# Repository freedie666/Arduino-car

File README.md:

# Arduino Car
  
Robotic car that follows line drawn on the ground using arduino.

Project was created at BUT-FIT

, class IMR.

## What robot does

> - Follows line at the ground
> - Can detect extra line that tells robot where to go at the crossroads
> - Extra lines can give robot additional orders
> - Detection of obstacle on the line
> - Robot can find best way around obstacle and avoid it
> - Is able to carry cargo and unload it on command
> - Sings a song when detects obstacle
> - Has multiple Blue and RED LEDs that show its intentions
> - Carries its own power source - batteries

## How its done

> - Brain of the operation is Arduino UNO
> - Car is powered by two 12V DC motors with gearbox
> - Motors are controlled by motor driver LV8406 using PWM
> - Lines are detected by infrared emiting LED and phototransistor [3x LED and 4x phototransistors]
> - Speed and directions are controlled by P-regulator
> - Obstacles are detected with ultrasonic sensor HC-SR04 
> - Ultrasonic sensor is mounted on small servo, providing range of detection up to +-90° 
> - Cargo beds movement is provided by stepper motor 2BYJ-48
> - Blue and RED LEDs are controlled by WS2818B led driver
> - Buzzer can play All star song which is stored in Flash memory

## Last notes

> - Everything electical is soldered at custom made PCB which fits onto Arduino as Arduino shield
> - Song is stacked in memory in a way to save as much memory as possible [4 numbers in one unsigned short]
  
## Links 
Demonstration of car at [Youtube](https://www.youtube.com/watch?v=gtERXzQzxGM)

More photos and videos at [Google Drive](https://drive.google.com/drive/folders/1pzaO6EnN3uHb_-Xj_Ckr5q-n50d8h_We?usp=sharing)

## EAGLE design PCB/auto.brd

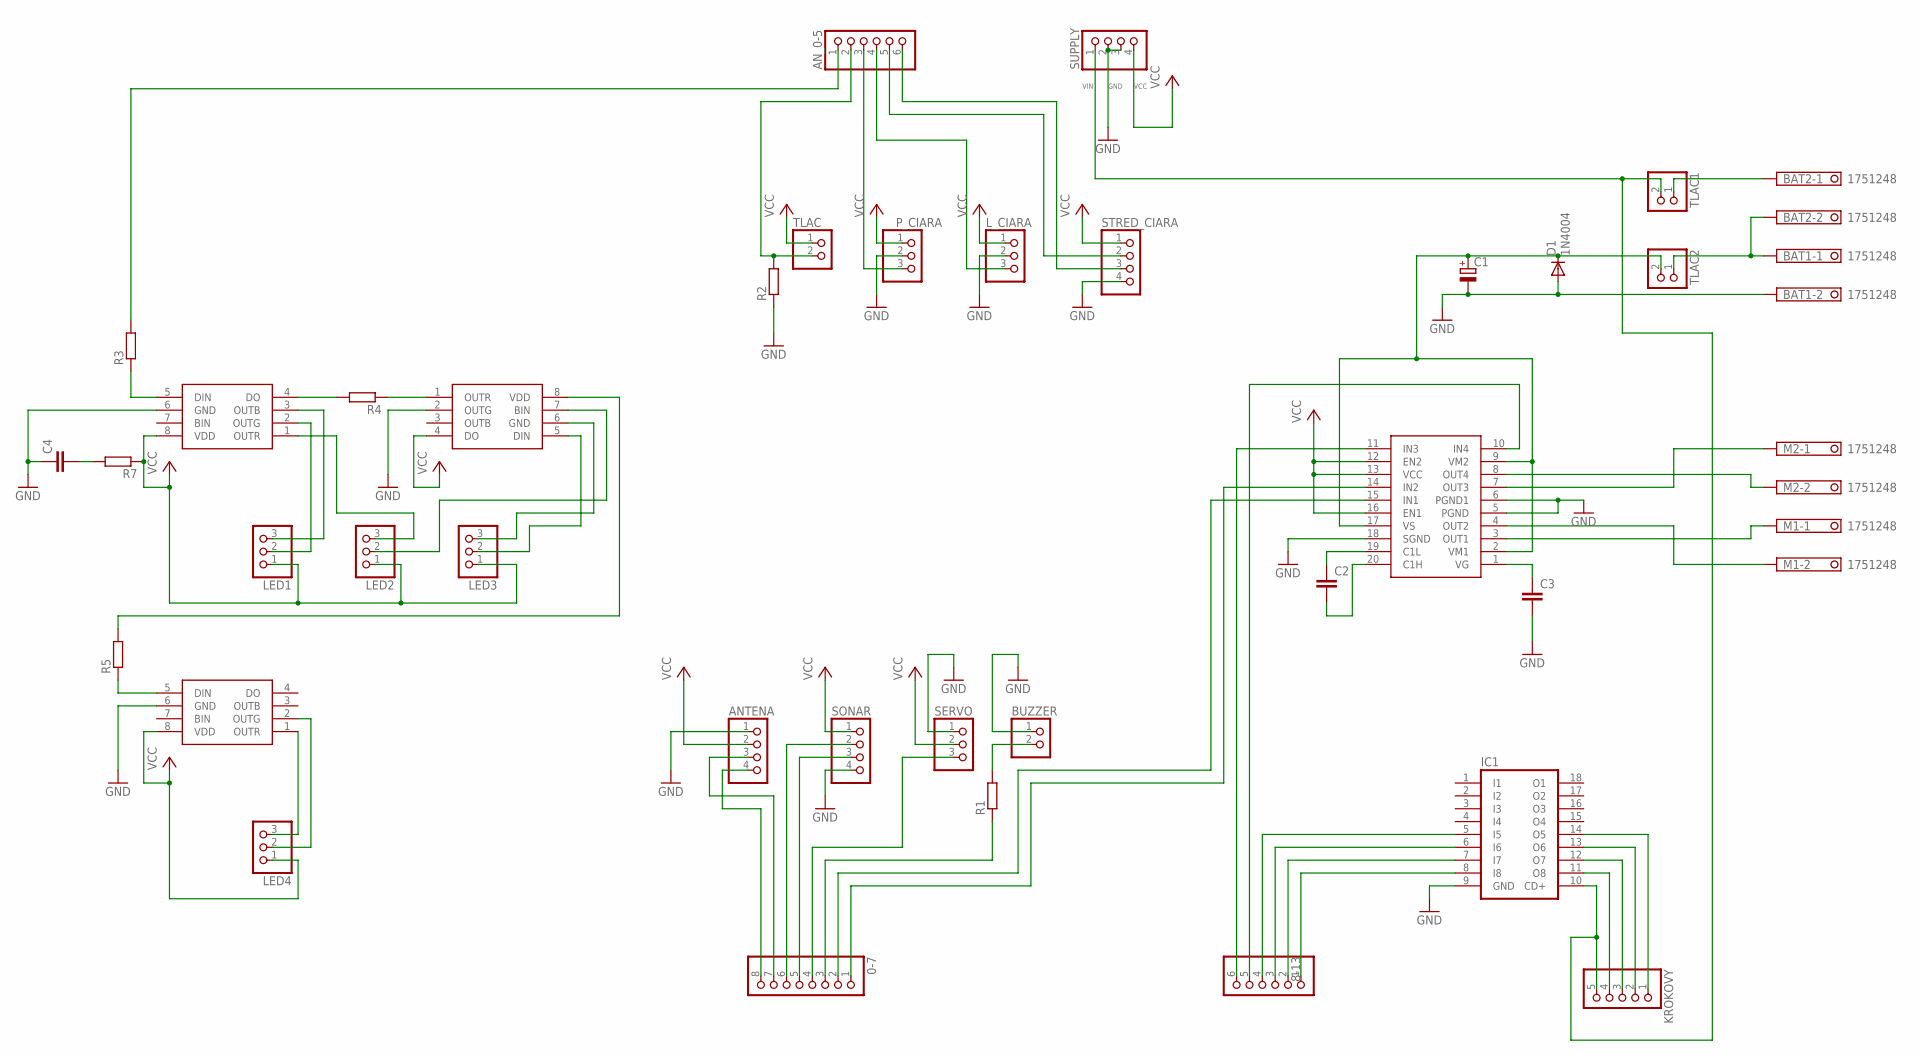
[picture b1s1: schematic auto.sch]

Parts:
0-7: PINHD-1X8; 1X08
8-13: PINHD-1X6; 1X06
ANTENA: PINHD-1X4; 1X04
AN_0-5: PINHD-1X6; 1X06
BAT1, BAT2: 1751248
BUZZER: PINHD-1X2; 1X02
C1: CPOL-EUE3.5-8; E3,5-8
C2, C3, C4: C-EU050-024X044; C050-024X044
D1: 1N4004; DO41-10
IC1: ULN2804A; DIL18
KROKOVY: PINHD-1X5; 1X05
LED1, LED2, LED3, LED4: PINHD-1X3; 1X03
L_CIARA: PINHD-1X3; 1X03
M1, M2: 1751248
P_CIARA: PINHD-1X3; 1X03
R1, R2, R3, R4, R5, R7: R0207/10; 0207/10
SERVO: PINHD-1X3; 1X03
SONAR: PINHD-1X4; 1X04
STRED_CIARA: PINHD-1X4; 1X04
SUPPLY: PINHD-1X4; 1X04
TLAC, TLAC1, TLAC2: PINHD-1X2; 1X02
U$1: LV8406; TSSOP20
U$2, U$3, U$4: WS2518B; SOP08

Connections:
GND: ANTENA.1, BAT1.2, BUZZER.1, C1.-, C3.2, C4.1, D1.A, IC1.9 (GND), L_CIARA.2, P_CIARA.2, R2.1, SERVO.1, SONAR.4, STRED_CIARA.4, SUPPLY.2, SUPPLY.3, U$1.5 (PGND), U$1.6 (PGND1), U$1.18 (SGND), U$2.6 (GND), U$3.2 (OUTG), U$4.6 (GND)
unnamed: AN_0-5.6, STRED_CIARA.3
unnamed: AN_0-5.5, STRED_CIARA.2
unnamed: AN_0-5.4, L_CIARA.3
unnamed: AN_0-5.3, P_CIARA.3
unnamed: 0-7.6, SONAR.2
unnamed: 0-7.5, SONAR.3
unnamed: 0-7.4, SERVO.3
unnamed: C3.1, U$1.1 (VG)
unnamed: BAT1.1, BAT2.2, TLAC2.1
unnamed: BUZZER.2, R1.2
unnamed: 0-7.3, R1.1
unnamed: BAT2.1, TLAC1.1
unnamed: 8-13.4, IC1.5 (I5)
unnamed: 8-13.3, IC1.6 (I6)
unnamed: 8-13.2, IC1.7 (I7)
unnamed: 8-13.1, IC1.8 (I8)
unnamed: M1.1, U$1.3 (OUT1)
unnamed: IC1.11 (O8), KROKOVY.4
unnamed: IC1.12 (O7), KROKOVY.3
unnamed: IC1.14 (O5), KROKOVY.1
unnamed: IC1.13 (O6), KROKOVY.2
unnamed: M1.2, U$1.4 (OUT2)
unnamed: M2.1, U$1.7 (OUT3)
unnamed: M2.2, U$1.8 (OUT4)
unnamed: C1.+, D1.C, TLAC2.2, U$1.2 (VM1), U$1.9 (VM2), U$1.17 (VS)
unnamed: 8-13.5, U$1.10 (IN4)
unnamed: 8-13.6, U$1.11 (IN3)
unnamed: C2.1, U$1.19 (C1L)
unnamed: C2.2, U$1.20 (C1H)
unnamed: R5.1, U$4.5 (DIN)
unnamed: LED4.3, U$4.1 (OUTR)
unnamed: 0-7.1, U$1.14 (IN2)
unnamed: R5.2, U$3.8 (VDD)
unnamed: AN_0-5.1, R3.2
unnamed: LED2.2, U$3.7 (BIN)
unnamed: LED1.3, U$2.3 (OUTB)
unnamed: LED4.2, U$4.2 (OUTG)
unnamed: R4.1, U$3.1 (OUTR)
unnamed: R3.1, U$2.5 (DIN)
unnamed: LED3.3, U$3.6 (GND)
unnamed: LED3.2, U$3.5 (DIN)
unnamed: AN_0-5.2, R2.2, TLAC.2
unnamed: 0-7.2, U$1.15 (IN1)
unnamed: LED1.2, U$2.2 (OUTG)
unnamed: 0-7.7, ANTENA.3
unnamed: 0-7.8, ANTENA.4
unnamed: R4.2, U$2.4 (DO)
unnamed: LED2.3, U$2.1 (OUTR)
unnamed: C4.2, R7.2
VCC: ANTENA.2, LED1.1, LED2.1, LED3.1, LED4.1, L_CIARA.1, P_CIARA.1, R7.1, SERVO.2, SONAR.1, STRED_CIARA.1, SUPPLY.4, TLAC.1, U$1.12 (EN2), U$1.13 (VCC), U$1.16 (EN1), U$2.8 (VDD), U$3.4 (DO), U$4.8 (VDD)
VIN: IC1.10 (CD+), KROKOVY.5, SUPPLY.1, TLAC1.2

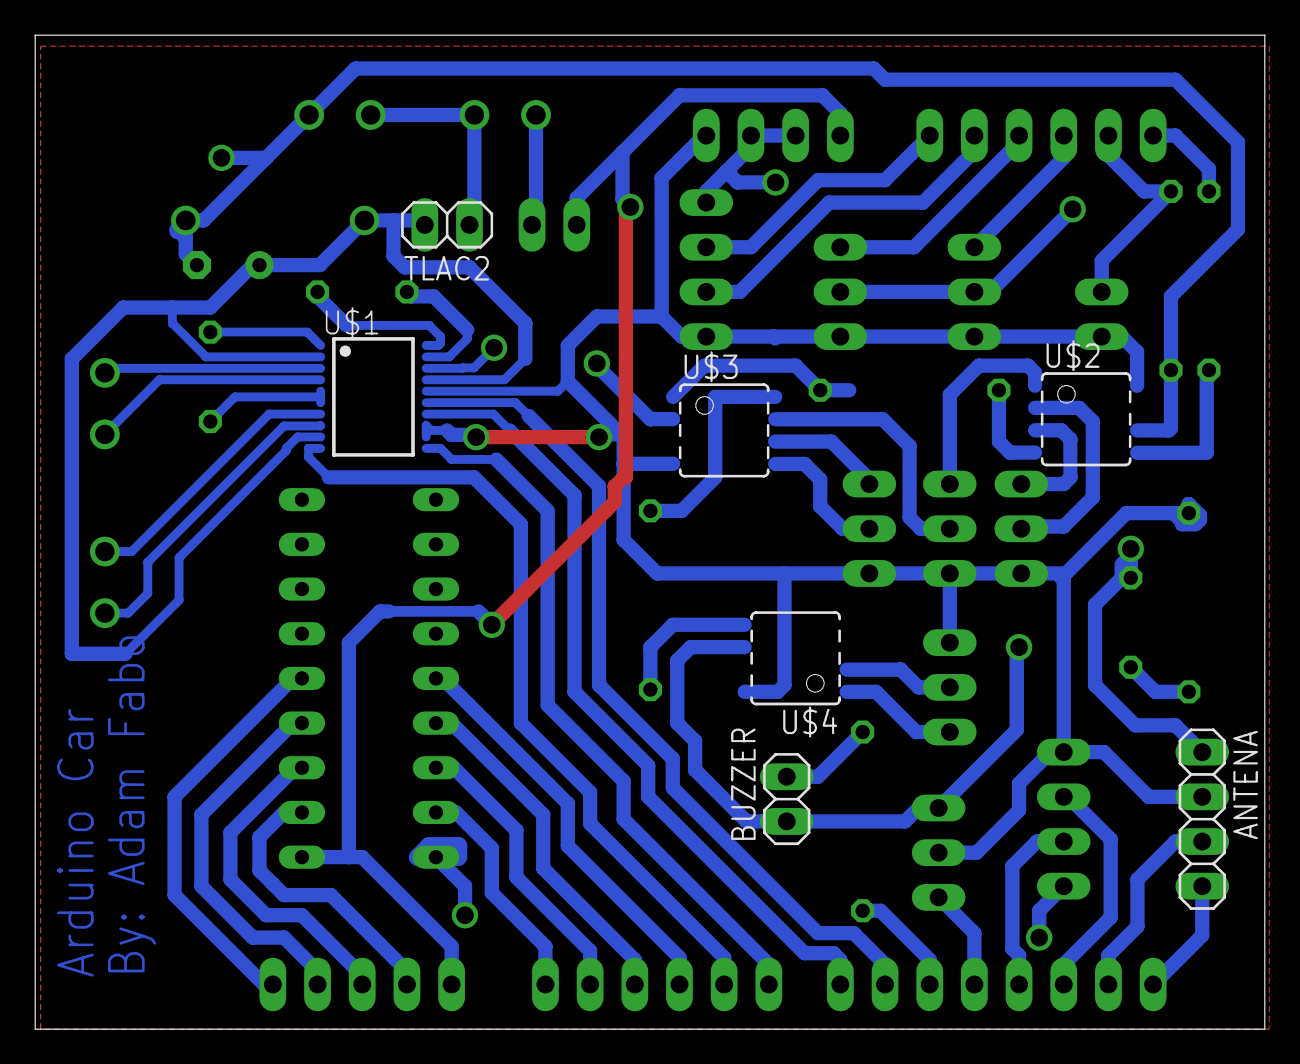
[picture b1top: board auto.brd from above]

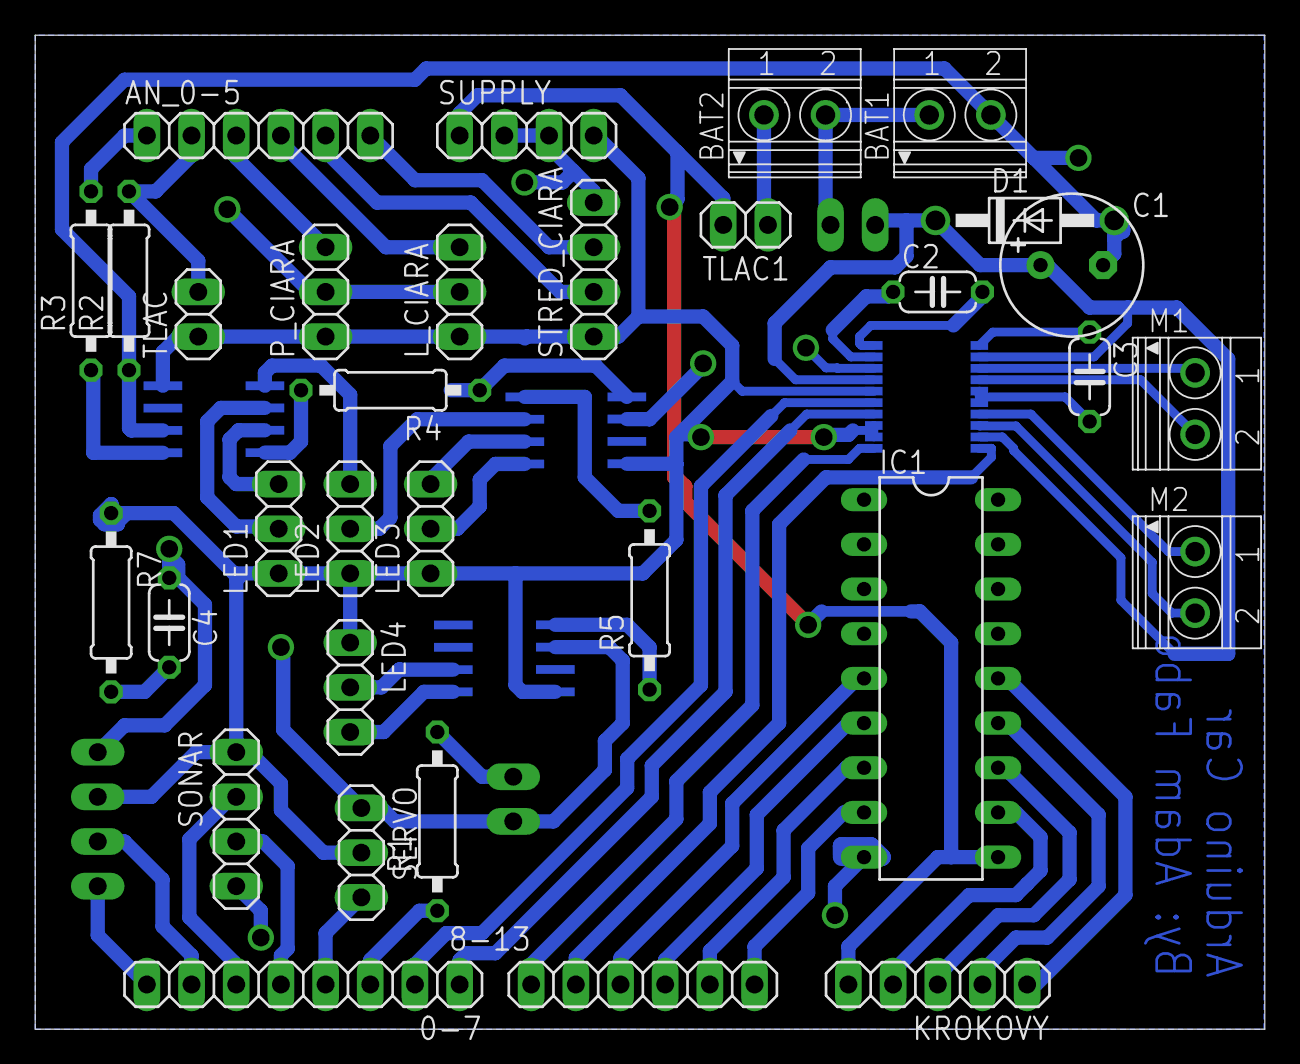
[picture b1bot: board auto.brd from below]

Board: 2 copper layers, 69.9 x 56.5 mm, 39 parts (32 on the bottom side), 52 nets.

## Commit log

2021-04-28 Create yo
2022-03-07 Create delete
